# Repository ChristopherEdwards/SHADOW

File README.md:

Introducing S.H.A.D.O.W. (Small Handheld Arduino Droid Operating Wand) MSE Edition
A MSE droid control system based on DanF's Padawan, and Darren Blum's S.H.A.D.O.W. that uses a PS3 Move Navigation Controller

This is a fork of Darren Blum's S.H.A.D.O.W. system. It is specifically modified to support MSE (RC Car) Based Droids.

It is a slimmed down version of the original code base to only support what is used on these types of droids.
If you are already familiar with S.H.A.D.O.W. then this fork will feel very familiar.

This sketch works on an Arduino MEGA ADK, or Arduino MEGA or Arduino UNO with a USB Shield

The sketch supports the following MP3 players:

* Sparkfun MP3Trigger: https://www.sparkfun.com/products/13720
* MDFly MP3 Player: http://www.mdfly.com/products/sd-card-mp3-player-module-rs232-ttl.html
* Rouge MP3: https://roguerobotics.com/products/rmp3

Pin Assignment:
* Steering Servo: 4
* ESC: 3
* MP3 Trigger: 2

Sound Mapping:
Note: when using L2 Throttle the L2 + and L1 + keystrokes still work, though they may not be very useful
* D-pad Up - Sound 001
* D-pad Right - Sound 002
* D-pad Down - Sound 003
* D-pad Left - Random Sound 001-015
* Circle/L2 + D-pad Up - Sound 004
* Cross/L2 + D-pad Right - Sound 005
* Not Available/L2 + D-pad Down - Sound 006
* Not Available/L2 + D-pad Left - Sound 015
* L1 + D-pad Up - Volume Up
* L1 + D-pad Right - Sound 019
* L1 + D-pad Down - Volume Down
* L1 + D-pad Left - Sound 018

Additional information for the original S.H.A.D.O.W. Sketch can be found in this thread on Asromech.net:
http://astromech.net/forums/showthread.php?19298-S-H-A-D-O-W-Padawan-based-mini-PS3-Controller

All libraries distributed with original licenses as specified by the library.
serMP3 library comes from: https://forum.arduino.cc/index.php?topic=148983.0

Thank you to:
* Darren Blum aka KnightShade - S.H.A.D.O.W Sketch and rMP3 support
* MSE Droid Builders Facebook page
* Ben Black - MDFly Support
* Joe McFly - Testing support

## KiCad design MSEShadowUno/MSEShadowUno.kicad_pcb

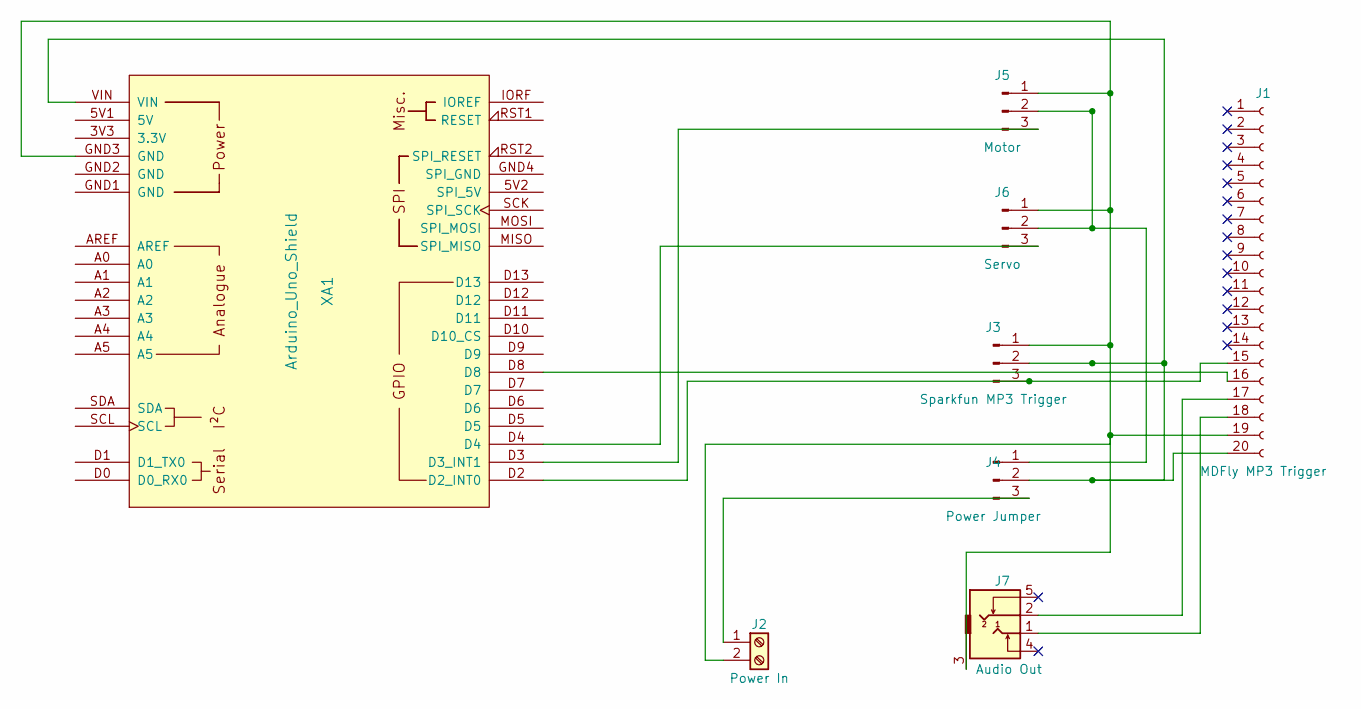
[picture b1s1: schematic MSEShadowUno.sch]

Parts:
J1: MDFly MP3 Trigger; Pin_Header_Straight_1x20_Pitch2.54mm
J2: Power In; TerminalBlock_Phoenix_MKDS1.5-2pol
J3: Sparkfun MP3 Trigger; Pin_Header_Straight_1x03_Pitch2.54mm
J4: Power Jumper; Pin_Header_Straight_1x03_Pitch2.54mm
J5: Motor; Pin_Header_Straight_1x03_Pitch2.54mm
J6: Servo; Pin_Header_Straight_1x03_Pitch2.54mm
J7: Audio Out; Stereo_Jack_3.5mm_Switch_Ledino_KB3SPRS
XA1: Arduino_Uno_Shield; Arduino_Uno_Shield_No_ICSP

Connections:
unnamed: J1.15, J3.3, XA1.D2 (D2_INT0)
unnamed: J1.16, XA1.D8
unnamed: J1.17, J7.2
unnamed: J1.18, J7.1
unnamed: J1.19, J2.2, J3.1, J5.1, J6.1, J7.3, XA1.GND3 (GND)
unnamed: J1.20, J3.2, J4.2, XA1.VIN
unnamed: J2.1, J4.3
unnamed: J4.1, J5.2, J6.2
unnamed: J5.3, XA1.D3 (D3_INT1)
unnamed: J6.3, XA1.D4

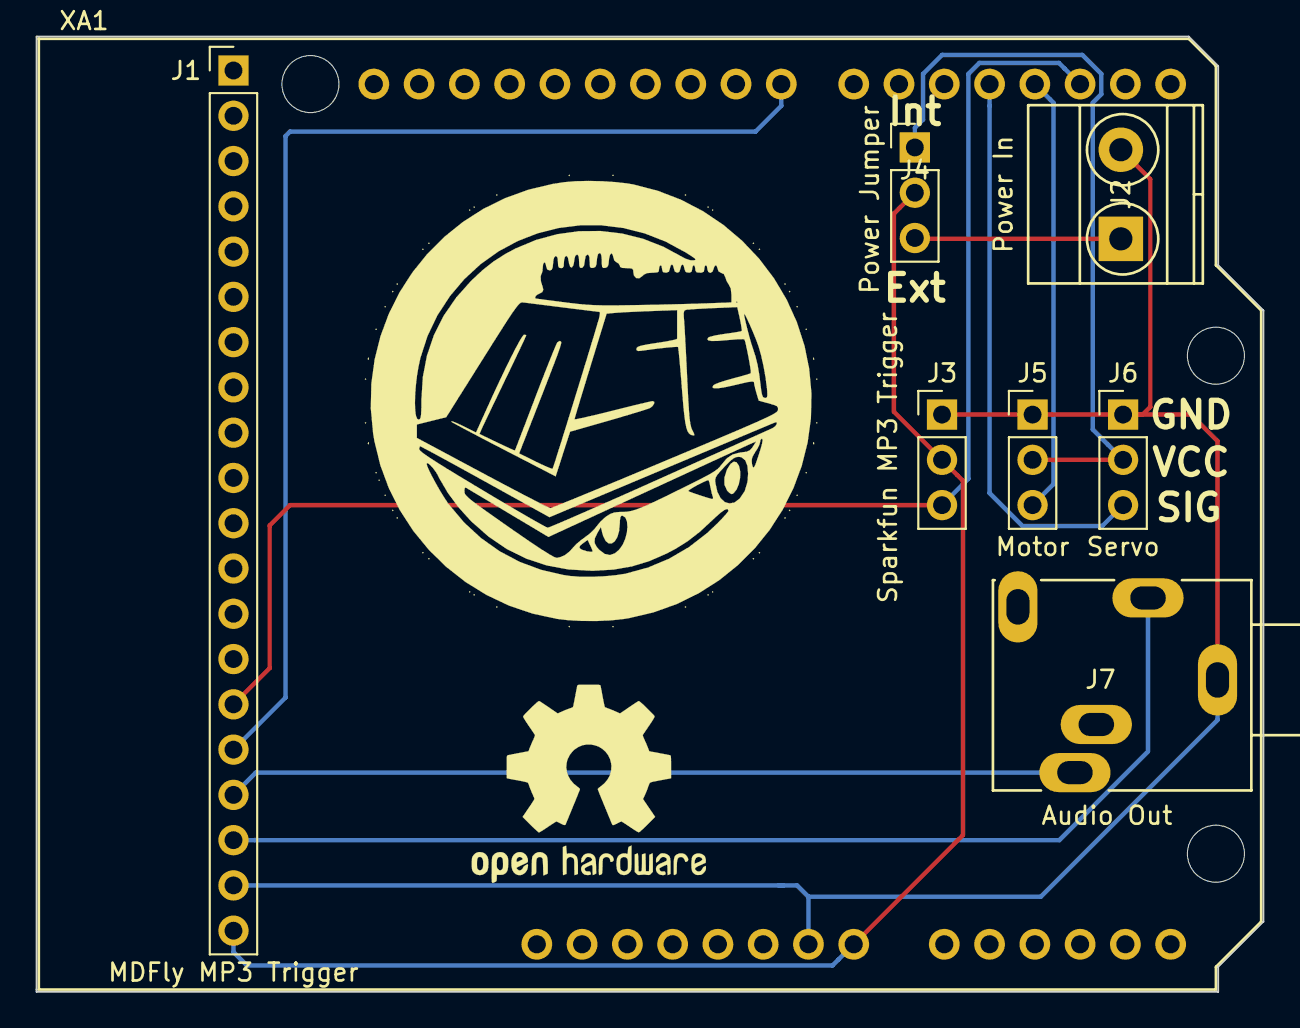
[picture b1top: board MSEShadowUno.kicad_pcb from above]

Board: 2 copper layers, 68.8 x 53.6 mm, 8 parts (0 on the bottom side), 10 nets.

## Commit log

2015-03-15 checkin of stable codebase
2015-03-15 Renamed History file
2017-11-21 Move sketch to folder with the same name
    The arduino IDE requires that the sketch be in a folder with the
    same name with nothing else in it.
2017-11-21 Initial MSE Edition sketch
    Modifications required to drive an RC Car (MSE Droid) using the sketch
    Defaults to using the Sparkfun MP3 Trigger instead of CFIII
2017-11-21 Implement L2 throttle and slim code base even more
    Use L2 for throttle to allow for better steering
    Remove code not used for MSE Droids
    Slim code base to support Arduino UNO
2017-11-21 Add Arduino UNO sized shield design
2017-11-21 Fix formatting of README
2017-11-21 Update Readme for slimmed down sketch
    Arduino pins moved around and additional sound buttons are mapped
2017-11-21 Fix more formatting of README.md
2017-11-23 Change pin assignments to work with USB host shields
    Completed testing on Arduino UNO and USB Host Shield, which now works
    Beware of the ICSP pin duplication on the Digital pins 9-13, these
    are effictively unusable pins now.
2017-11-23 Add MDFly MP3 player support
    Thanks to Ben Black for the MDFly MP3 Player support.
    * Integrated provided code to support either the Sparkfun MP3Trigger or
    the MDFly MP3 Player
    * Updated README with board URLs
    * Fixed formatting of sketch
    * Make sure the MP3 Player Pin is configurable
2017-11-23 Add attribution info for libraries
2017-11-23 Fix steering bug
    The previous code would only allow steering if throttle input was given
2017-12-28 Incorporate changes from Zach Tyke
    Random Trigger = L3, also available with L2+L3
2018-04-26 Update PCB Board Shield
2018-05-17 Add KiCad board layout
2018-07-29 Update PCB Board
    Update PCB board to use Arduino Uno Shield instead of Atmel chip
    (this fixes routing problems between the schematic and PCB)
    Remove generated Gerber files
2018-07-29 Add gitignore for gerber files and backups
    Gerber files are generated from KiCad and shouldn't be version controlled
    Backup files are unnecessary to be version controlled
2018-07-29 Integrate changes from Hotshot7997/Akillermethod for Traxxas Bandit
2018-08-12 Fix issues with Joystick throttle, add reverse steering option
    * Joystick throttle didn't work due to refering to a changed variable
    name for the joystick deadzone. Change to proper variable name
    * Add reverse steering option so left and right always refer to the
    correct direction, but the output from the arduino is reveresed
    * Cleaned up comment formatting
2018-10-06 Fix reverse steering option
    Inadvertently didn't apply the reverse steering option to L2 Throttle
2018-10-07 Volume control case logic had +/- swapped
2018-10-07 Integrate changes to support Rogue rMP3 trigger
    Contribution from Daren Blum
    Add ifdefs to support rMP3 trigger in various spots
    Add support for 2 new sound commands (L1 + CIRCLE & L1 + CROSS)
    Add RogueMp3 library
    Update Readme with rMP3 link and contribution info
2018-10-21 Integrate Ryan Diaz's changes to prevent duplicate sounds
    Ryan Diaz provided changes to prevent duplicate sounds and a sound
    to key map (PS3NavButtonMap.txt)
2019-04-03 Typo
2019-04-03 Ignore build and vscode folders
2019-04-03 Fix for MAC address padding
